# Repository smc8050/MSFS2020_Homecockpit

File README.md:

# MSFS2020 Homecockpit
The aim of this project was to build a home cockpit working together with Microsoft Flight Simulator 2020.
A "How to use it" will be published in future...

The PCB files are best viewed on [cadlab.io](https://cadlab.io/project/23795/main/files/PCB)

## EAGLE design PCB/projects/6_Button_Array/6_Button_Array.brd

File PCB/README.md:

# PCB directory
This directory contains all the PCB files, needed for the Cockpit panel. An overview will be uploaded in future...

For better visualization of the PCB's view this project on [CADLAB.io](https://cadlab.io/project/23795/main/files/PCB/projects). 

## Remarks
The zip files in the individual project folders are used to manufacture the pcb's and contain the gerber files. These will not be updated frequently, so you better build your own gerber files for production.

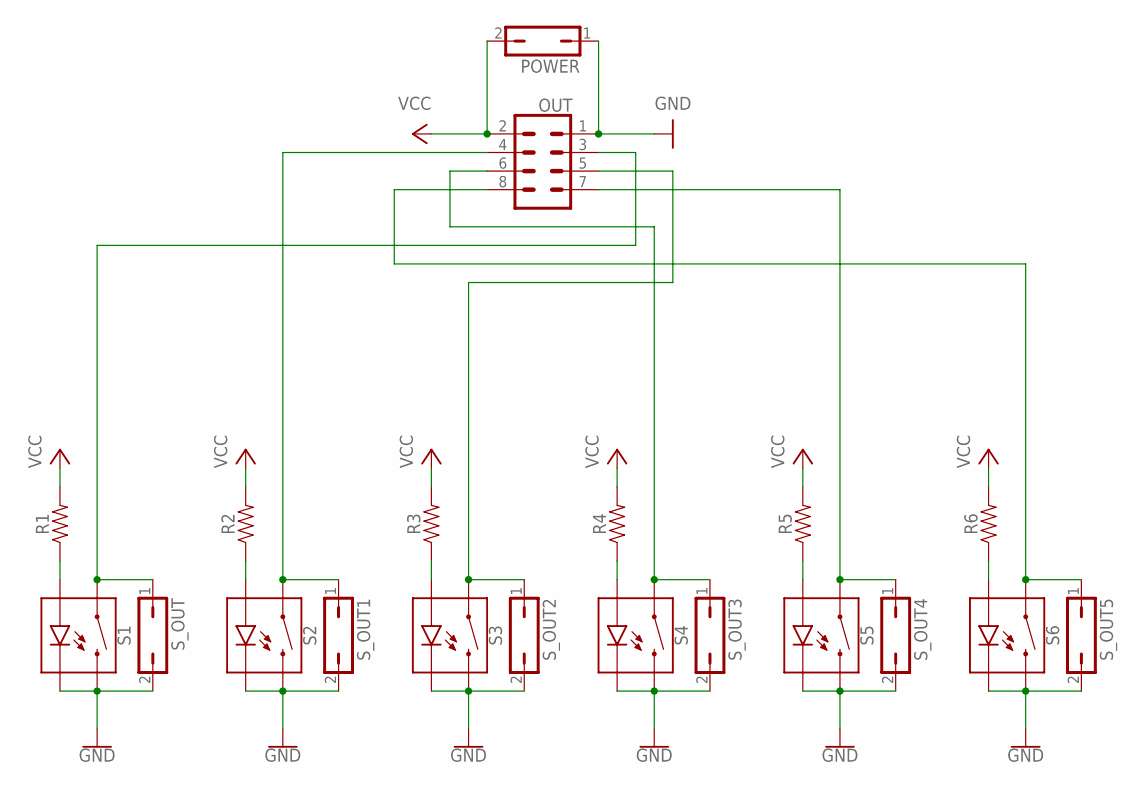
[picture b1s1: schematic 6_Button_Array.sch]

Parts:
OUT: CONN_04X2; 2X4
POWER: JP1Q; JP1
R1, R2, R3, R4, R5, R6: 1206
S1, S2, S3, S4, S5, S6: MOMENTARY-SWITCH-SPST-LED-PTH-12MM; TACTILE_SWITCH_LED_PTH_12MM
S_OUT, S_OUT1, S_OUT2, S_OUT3, S_OUT4, S_OUT5: JP1Q; JP1

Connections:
GND: OUT.1, POWER.1, S1.2, S1.C, S2.2, S2.C, S3.2, S3.C, S4.2, S4.C, S5.2, S5.C, S6.2, S6.C, S_OUT.2, S_OUT1.2, S_OUT2.2, S_OUT3.2, S_OUT4.2, S_OUT5.2
unnamed: R1.1, S1.A
unnamed: R2.1, S2.A
unnamed: R3.1, S3.A
unnamed: OUT.5, S3.4 (1), S_OUT2.1
unnamed: R4.1, S4.A
unnamed: OUT.6, S4.4 (1), S_OUT3.1
unnamed: R5.1, S5.A
unnamed: OUT.7, S5.4 (1), S_OUT4.1
unnamed: R6.1, S6.A
unnamed: OUT.3, S1.4 (1), S_OUT.1
unnamed: OUT.8, S6.4 (1), S_OUT5.1
unnamed: OUT.4, S2.4 (1), S_OUT1.1
VCC: OUT.2, POWER.2, R1.2, R2.2, R3.2, R4.2, R5.2, R6.2

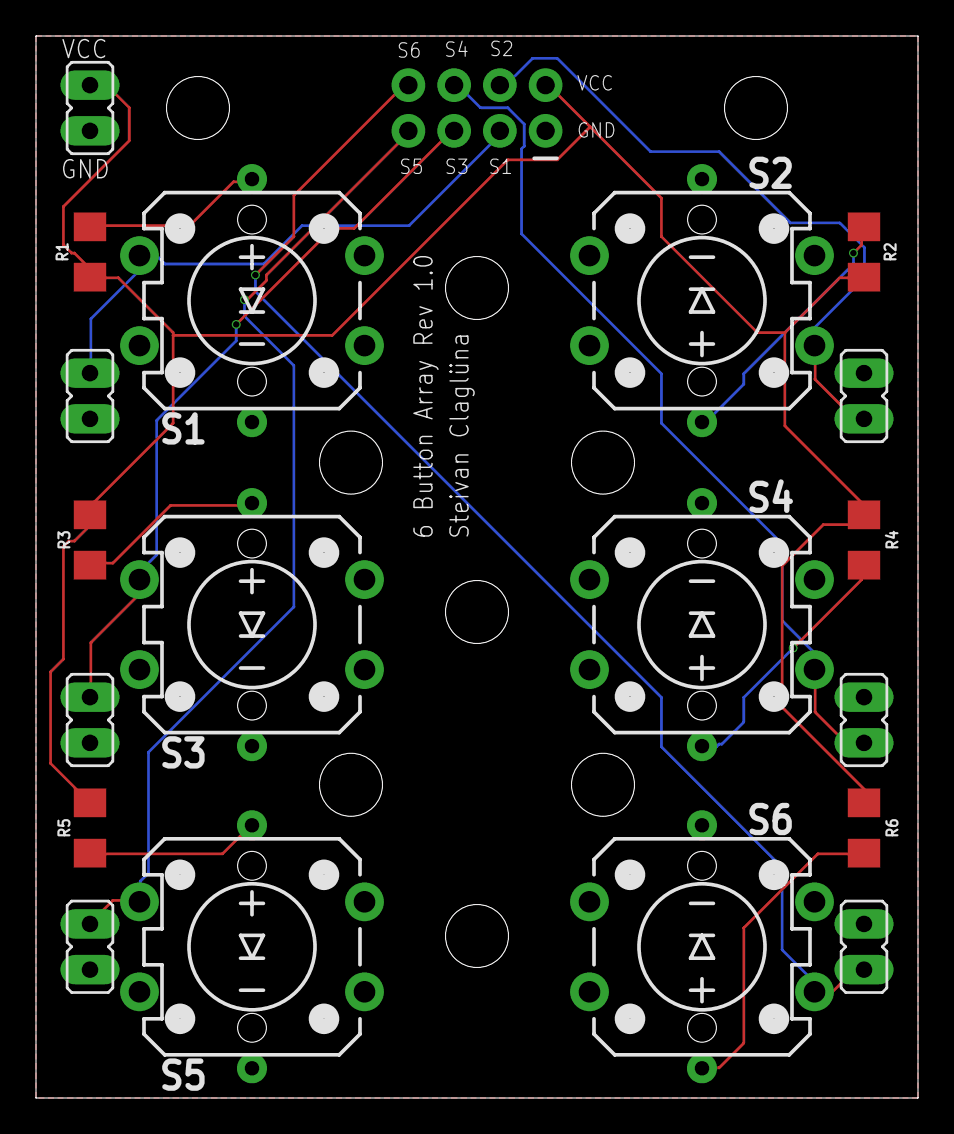
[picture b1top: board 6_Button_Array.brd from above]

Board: 2 copper layers, 49.0 x 59.0 mm, 20 parts (1 on the bottom side), 14 nets.

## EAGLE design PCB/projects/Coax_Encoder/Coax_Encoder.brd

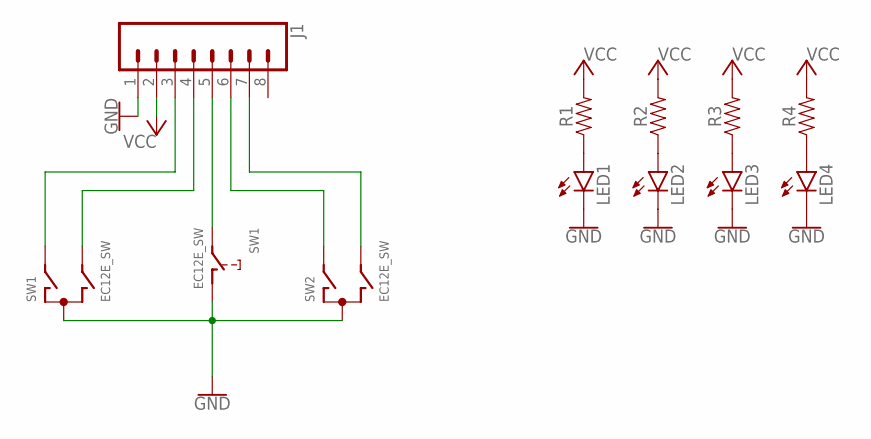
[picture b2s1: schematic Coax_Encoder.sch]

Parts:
J1: CONN_08"; 1X08
LED1, LED2, LED3, LED4: LED3MM
R1, R2, R3, R4: 1206
SW1, SW2: EC12E_SW; ALPS_EC12E_SW

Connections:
GND: J1.1, LED1.K (C), LED2.K (C), LED3.K (C), LED4.K (C), SW1.C, SW1.D (1), SW2.C
unnamed: J1.3, SW1.A
unnamed: J1.4, SW1.B
unnamed: J1.5, SW1.E (2)
unnamed: J1.6, SW2.A
unnamed: J1.7, SW2.B
unnamed: LED1.A, R1.1
unnamed: LED2.A, R2.1
unnamed: LED3.A, R3.1
unnamed: LED4.A, R4.1
VCC: J1.2, R1.2, R2.2, R3.2, R4.2

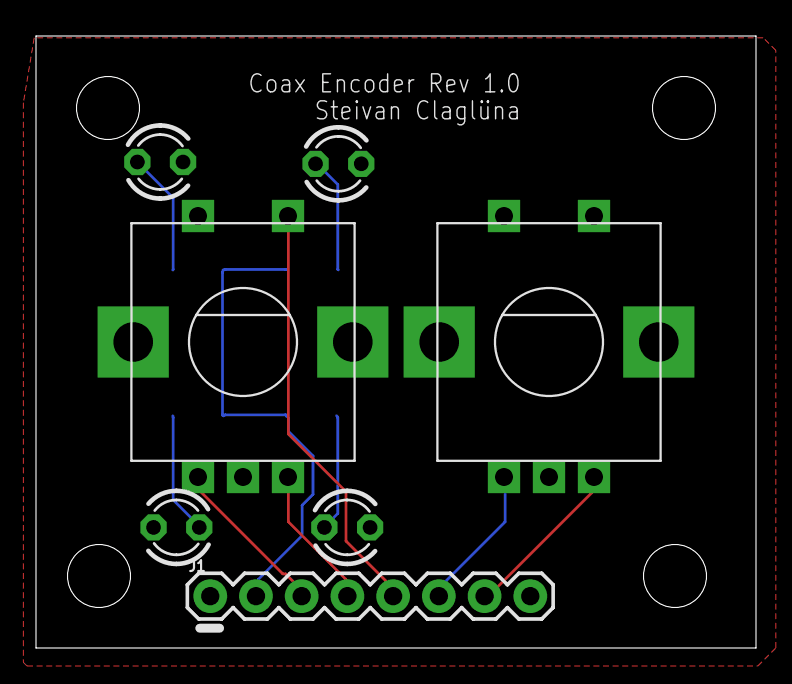
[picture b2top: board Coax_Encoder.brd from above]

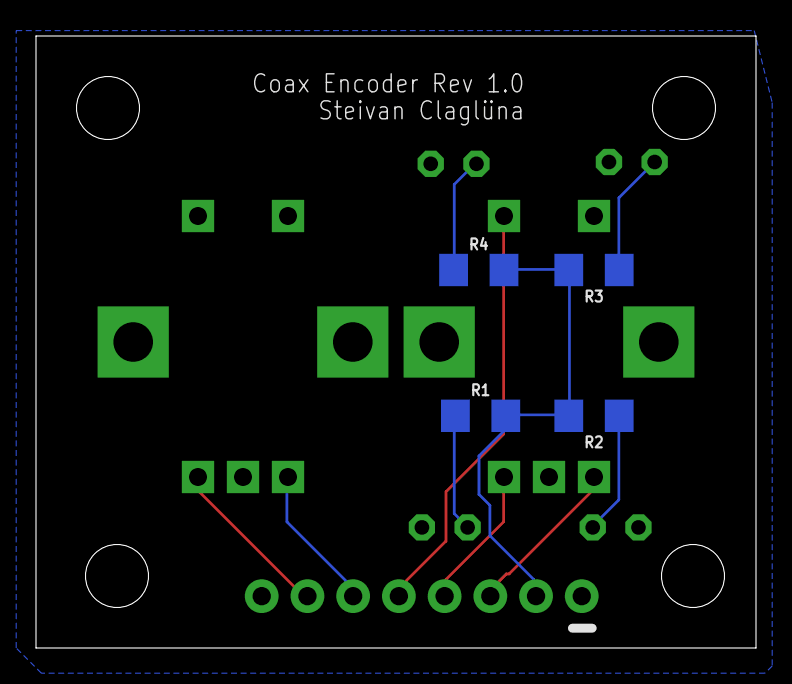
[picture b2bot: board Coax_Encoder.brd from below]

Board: 2 copper layers, 40.0 x 34.0 mm, 11 parts (4 on the bottom side), 11 nets.

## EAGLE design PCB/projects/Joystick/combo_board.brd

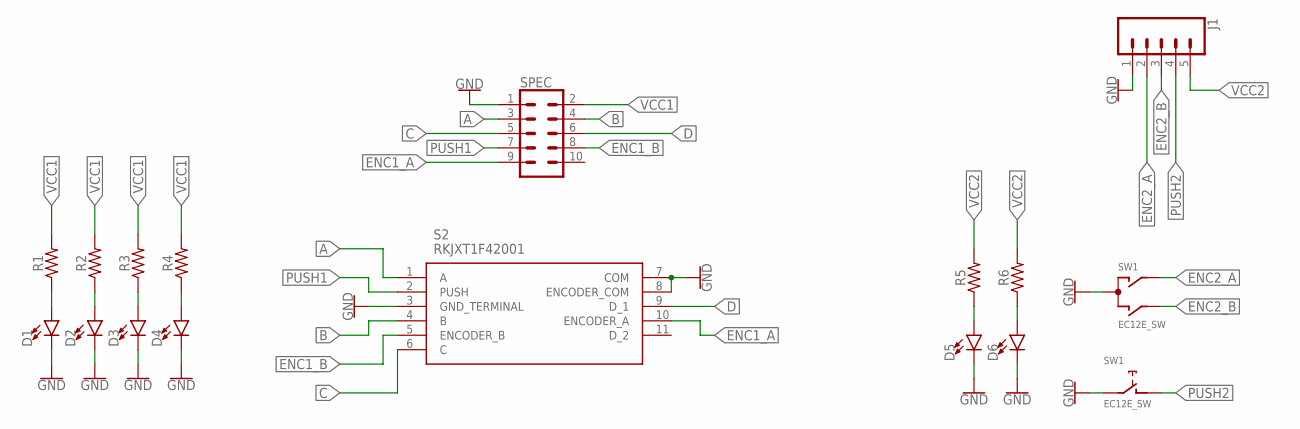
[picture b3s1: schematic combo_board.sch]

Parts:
D1, D2, D3, D4, D5, D6: LED-3MM-NO_SILK; LED_3MM-NS
J1: CONN_05; 1X05
R1, R2, R3, R4, R5, R6: 1206
S2: RKJXT1F42001
SPEC: CONN_05X2PTH; 2X5
SW1: EC12E_SW; ALPS_EC12E_SW

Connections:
A: S2.1 (A), SPEC.3
B: S2.4 (B), SPEC.4
C: S2.6 (C), SPEC.5
D: S2.9 (D_1), SPEC.6
ENC1_A: S2.10 (ENCODER_A), SPEC.9
ENC1_B: S2.5 (ENCODER_B), SPEC.8
ENC2_A: J1.2, SW1.A
ENC2_B: J1.3, SW1.B
GND: D1.K (C), D2.K (C), D3.K (C), D4.K (C), D5.K (C), D6.K (C), J1.1, S2.3 (GND_TERMINAL), S2.7 (COM), S2.8 (ENCODER_COM), SPEC.1, SW1.C, SW1.E (2)
unnamed: D1.A, R1.1
unnamed: D2.A, R2.1
unnamed: D3.A, R3.1
unnamed: D4.A, R4.1
unnamed: D5.A, R5.1
unnamed: D6.A, R6.1
PUSH1: S2.2 (PUSH), SPEC.7
PUSH2: J1.4, SW1.D (1)
VCC1: R1.2, R2.2, R3.2, R4.2, SPEC.2
VCC2: J1.5, R5.2, R6.2

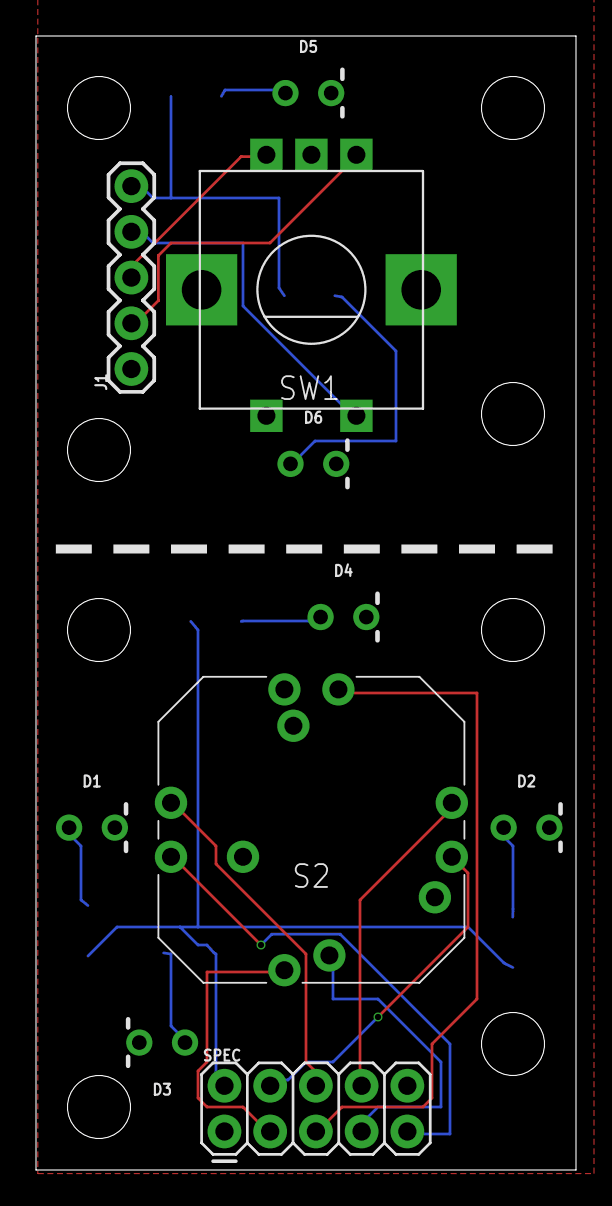
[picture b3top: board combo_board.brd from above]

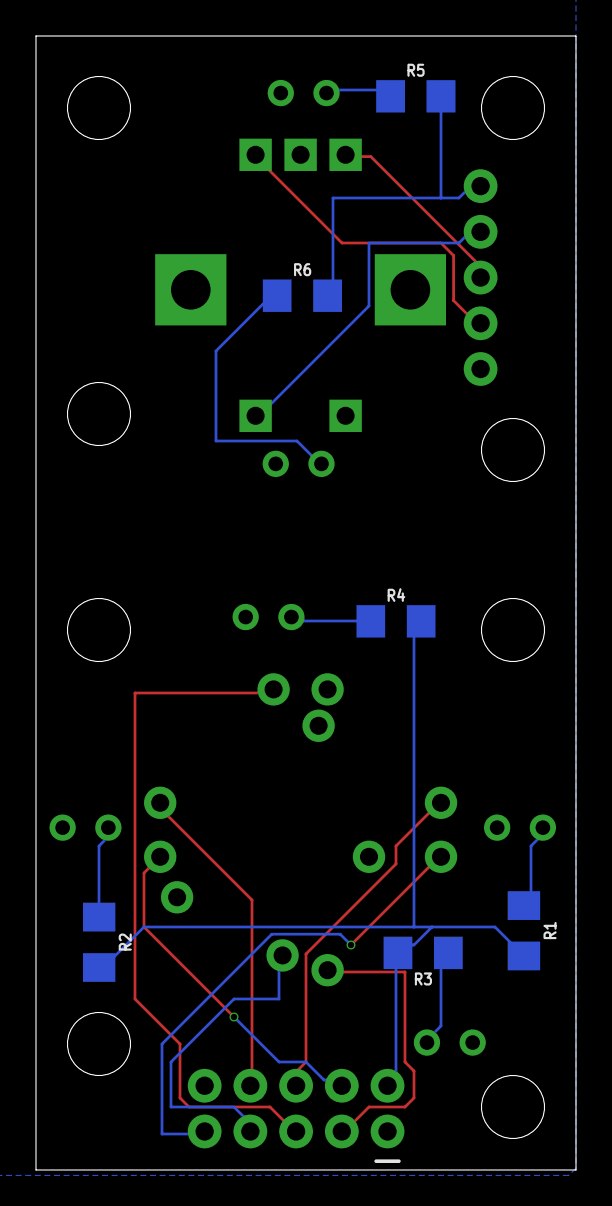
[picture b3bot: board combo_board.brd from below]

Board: 2 copper layers, 30.0 x 63.0 mm, 16 parts (6 on the bottom side), 19 nets.

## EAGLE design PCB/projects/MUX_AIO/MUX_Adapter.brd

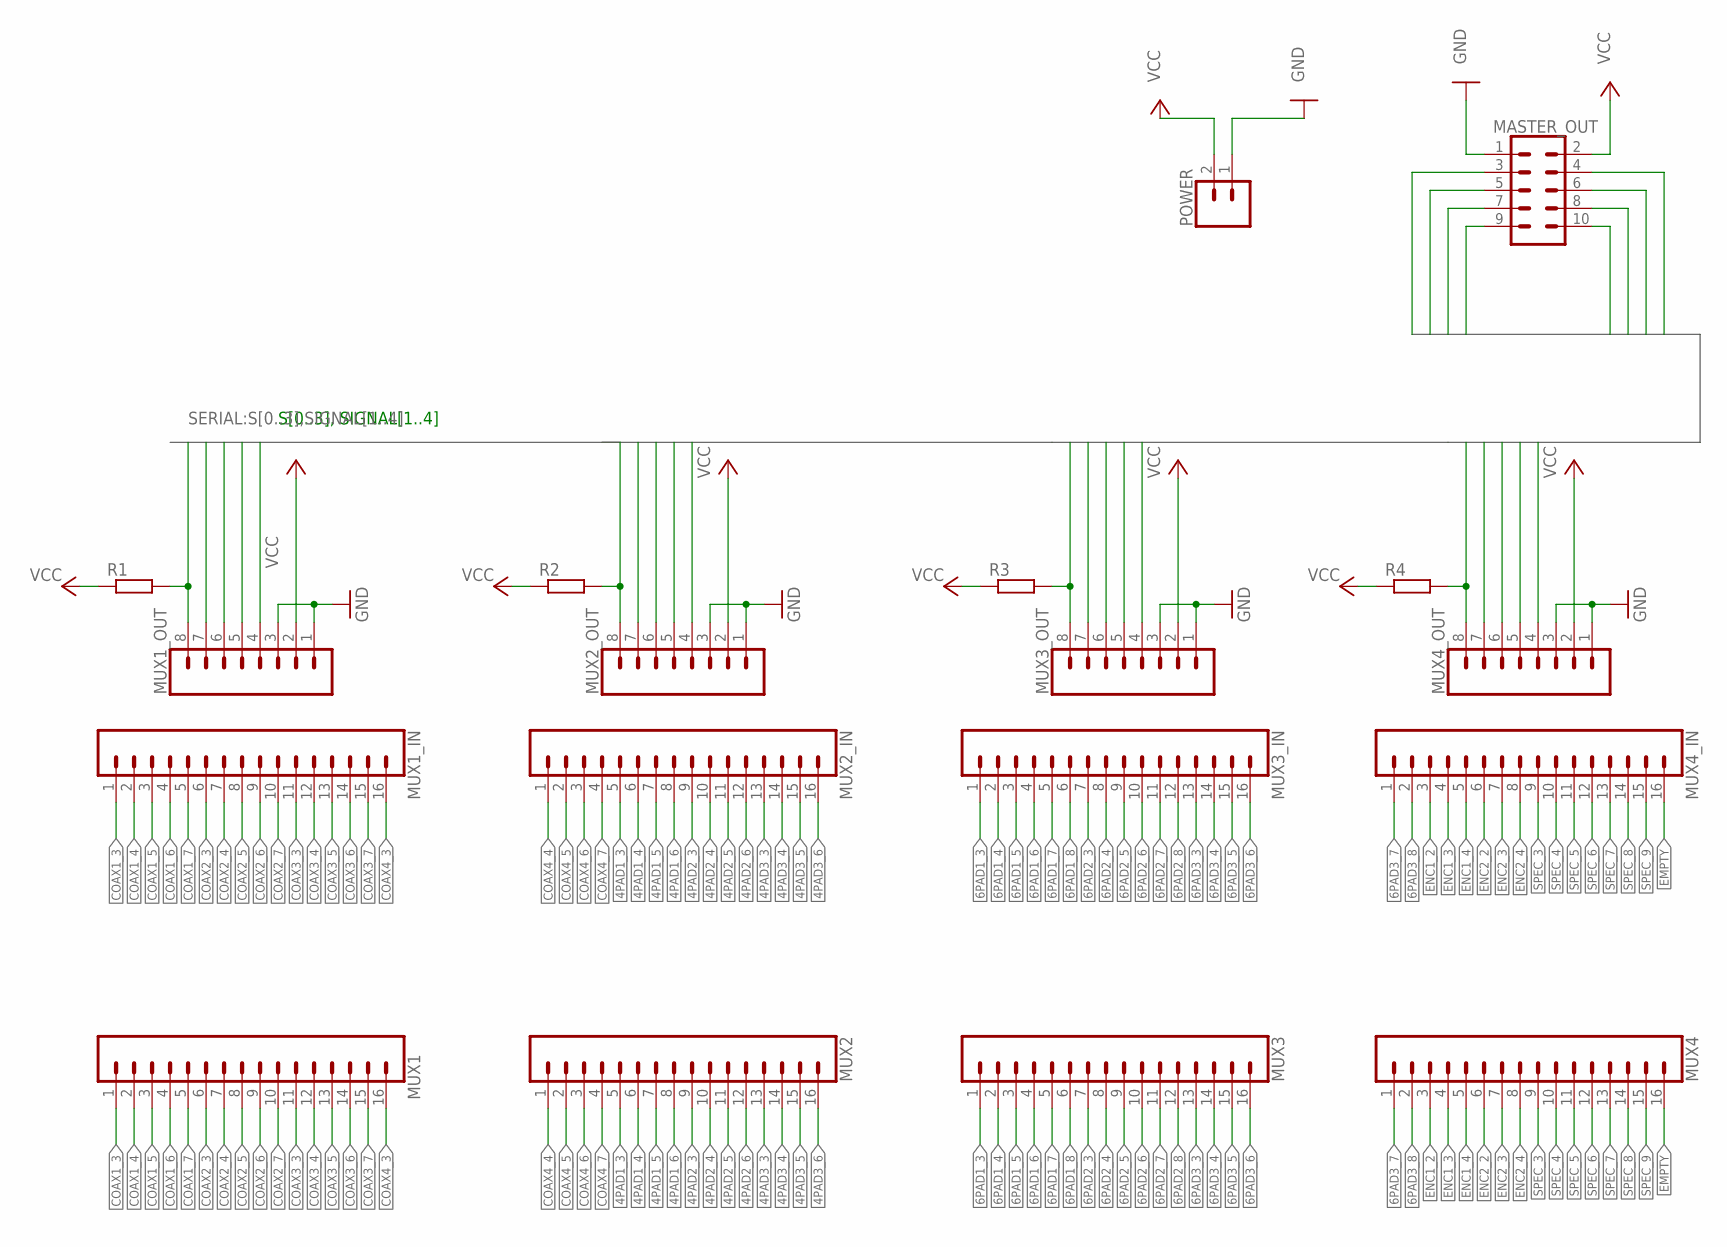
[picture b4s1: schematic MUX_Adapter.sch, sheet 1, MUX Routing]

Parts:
MASTER_OUT: CONN_05X2SHD-NS; 2X5-SHROUDED-NS
MUX1, MUX1_IN, MUX2, MUX2_IN, MUX3, MUX3_IN, MUX4, MUX4_IN: CONN_16; 1X16
MUX1_OUT, MUX2_OUT, MUX3_OUT, MUX4_OUT: CONN_08"; 1X08
POWER: CONN_02; 1X02
R1, R2, R3, R4: R-EU_0207/10; 0207/10

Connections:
4PAD1_3: MUX2.5, MUX2_IN.5; also elsewhere on the board
4PAD1_4: MUX2.6, MUX2_IN.6; also elsewhere on the board
4PAD1_5: MUX2.7, MUX2_IN.7; also elsewhere on the board
4PAD1_6: MUX2.8, MUX2_IN.8; also elsewhere on the board
4PAD2_3: MUX2.9, MUX2_IN.9; also elsewhere on the board
4PAD2_4: MUX2.10, MUX2_IN.10; also elsewhere on the board
4PAD2_5: MUX2.11, MUX2_IN.11; also elsewhere on the board
4PAD2_6: MUX2.12, MUX2_IN.12; also elsewhere on the board
4PAD3_3: MUX2.13, MUX2_IN.13; also elsewhere on the board
4PAD3_4: MUX2.14, MUX2_IN.14; also elsewhere on the board
4PAD3_5: MUX2.15, MUX2_IN.15; also elsewhere on the board
4PAD3_6: MUX2.16, MUX2_IN.16; also elsewhere on the board
6PAD1_3: MUX3.1, MUX3_IN.1; also elsewhere on the board
6PAD1_4: MUX3.2, MUX3_IN.2; also elsewhere on the board
6PAD1_5: MUX3.3, MUX3_IN.3; also elsewhere on the board
6PAD1_6: MUX3.4, MUX3_IN.4; also elsewhere on the board
6PAD1_7: MUX3.5, MUX3_IN.5; also elsewhere on the board
6PAD1_8: MUX3.6, MUX3_IN.6; also elsewhere on the board
6PAD2_3: MUX3.7, MUX3_IN.7; also elsewhere on the board
6PAD2_4: MUX3.8, MUX3_IN.8; also elsewhere on the board
6PAD2_5: MUX3.9, MUX3_IN.9; also elsewhere on the board
6PAD2_6: MUX3.10, MUX3_IN.10; also elsewhere on the board
6PAD2_7: MUX3.11, MUX3_IN.11; also elsewhere on the board
6PAD2_8: MUX3.12, MUX3_IN.12; also elsewhere on the board
6PAD3_3: MUX3.13, MUX3_IN.13; also elsewhere on the board
6PAD3_4: MUX3.14, MUX3_IN.14; also elsewhere on the board
6PAD3_5: MUX3.15, MUX3_IN.15; also elsewhere on the board
6PAD3_6: MUX3.16, MUX3_IN.16; also elsewhere on the board
6PAD3_7: MUX4.1, MUX4_IN.1; also elsewhere on the board
6PAD3_8: MUX4.2, MUX4_IN.2; also elsewhere on the board
COAX1_3: MUX1.1, MUX1_IN.1; also elsewhere on the board
COAX1_4: MUX1.2, MUX1_IN.2; also elsewhere on the board
COAX1_5: MUX1.3, MUX1_IN.3; also elsewhere on the board
COAX1_6: MUX1.4, MUX1_IN.4; also elsewhere on the board
COAX1_7: MUX1.5, MUX1_IN.5; also elsewhere on the board
COAX2_3: MUX1.6, MUX1_IN.6; also elsewhere on the board
COAX2_4: MUX1.7, MUX1_IN.7; also elsewhere on the board
COAX2_5: MUX1.8, MUX1_IN.8; also elsewhere on the board
COAX2_6: MUX1.9, MUX1_IN.9; also elsewhere on the board
COAX2_7: MUX1.10, MUX1_IN.10; also elsewhere on the board
COAX3_3: MUX1.11, MUX1_IN.11; also elsewhere on the board
COAX3_4: MUX1.12, MUX1_IN.12; also elsewhere on the board
COAX3_5: MUX1.13, MUX1_IN.13; also elsewhere on the board
COAX3_6: MUX1.14, MUX1_IN.14; also elsewhere on the board
COAX3_7: MUX1.15, MUX1_IN.15; also elsewhere on the board
COAX4_3: MUX1.16, MUX1_IN.16; also elsewhere on the board
COAX4_4: MUX2.1, MUX2_IN.1; also elsewhere on the board
COAX4_5: MUX2.2, MUX2_IN.2; also elsewhere on the board
COAX4_6: MUX2.3, MUX2_IN.3; also elsewhere on the board
COAX4_7: MUX2.4, MUX2_IN.4; also elsewhere on the board
EMPTY: MUX4.16, MUX4_IN.16
ENC1_2: MUX4.3, MUX4_IN.3; also elsewhere on the board
ENC1_3: MUX4.4, MUX4_IN.4; also elsewhere on the board
ENC1_4: MUX4.5, MUX4_IN.5; also elsewhere on the board
ENC2_2: MUX4.6, MUX4_IN.6; also elsewhere on the board
ENC2_3: MUX4.7, MUX4_IN.7; also elsewhere on the board
ENC2_4: MUX4.8, MUX4_IN.8; also elsewhere on the board
GND: MASTER_OUT.1, MUX1_OUT.1, MUX1_OUT.3, MUX2_OUT.1, MUX2_OUT.3, MUX3_OUT.1, MUX3_OUT.3, MUX4_OUT.1, MUX4_OUT.3, POWER.1; also elsewhere on the board
S0: MASTER_OUT.3, MUX1_OUT.4, MUX2_OUT.4, MUX3_OUT.4, MUX4_OUT.4
S1: MASTER_OUT.4, MUX1_OUT.5, MUX2_OUT.5, MUX3_OUT.5, MUX4_OUT.5
S2: MASTER_OUT.5, MUX1_OUT.6, MUX2_OUT.6, MUX3_OUT.6, MUX4_OUT.6
S3: MASTER_OUT.6, MUX1_OUT.7, MUX2_OUT.7, MUX3_OUT.7, MUX4_OUT.7
SIGNAL1: MASTER_OUT.7, MUX4_OUT.8, R4.2
SIGNAL2: MASTER_OUT.8, MUX3_OUT.8, R3.2
SIGNAL3: MASTER_OUT.9, MUX2_OUT.8, R2.2
SIGNAL4: MASTER_OUT.10, MUX1_OUT.8, R1.2
SPEC_3: MUX4.9, MUX4_IN.9; also elsewhere on the board
SPEC_4: MUX4.10, MUX4_IN.10; also elsewhere on the board
SPEC_5: MUX4.11, MUX4_IN.11; also elsewhere on the board
SPEC_6: MUX4.12, MUX4_IN.12; also elsewhere on the board
SPEC_7: MUX4.13, MUX4_IN.13; also elsewhere on the board
SPEC_8: MUX4.14, MUX4_IN.14; also elsewhere on the board
SPEC_9: MUX4.15, MUX4_IN.15; also elsewhere on the board
VCC: MASTER_OUT.2, MUX1_OUT.2, MUX2_OUT.2, MUX3_OUT.2, MUX4_OUT.2, POWER.2, R1.1, R2.1, R3.1, R4.1; also elsewhere on the board

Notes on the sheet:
S[0..3], SIGNAL[1..4]

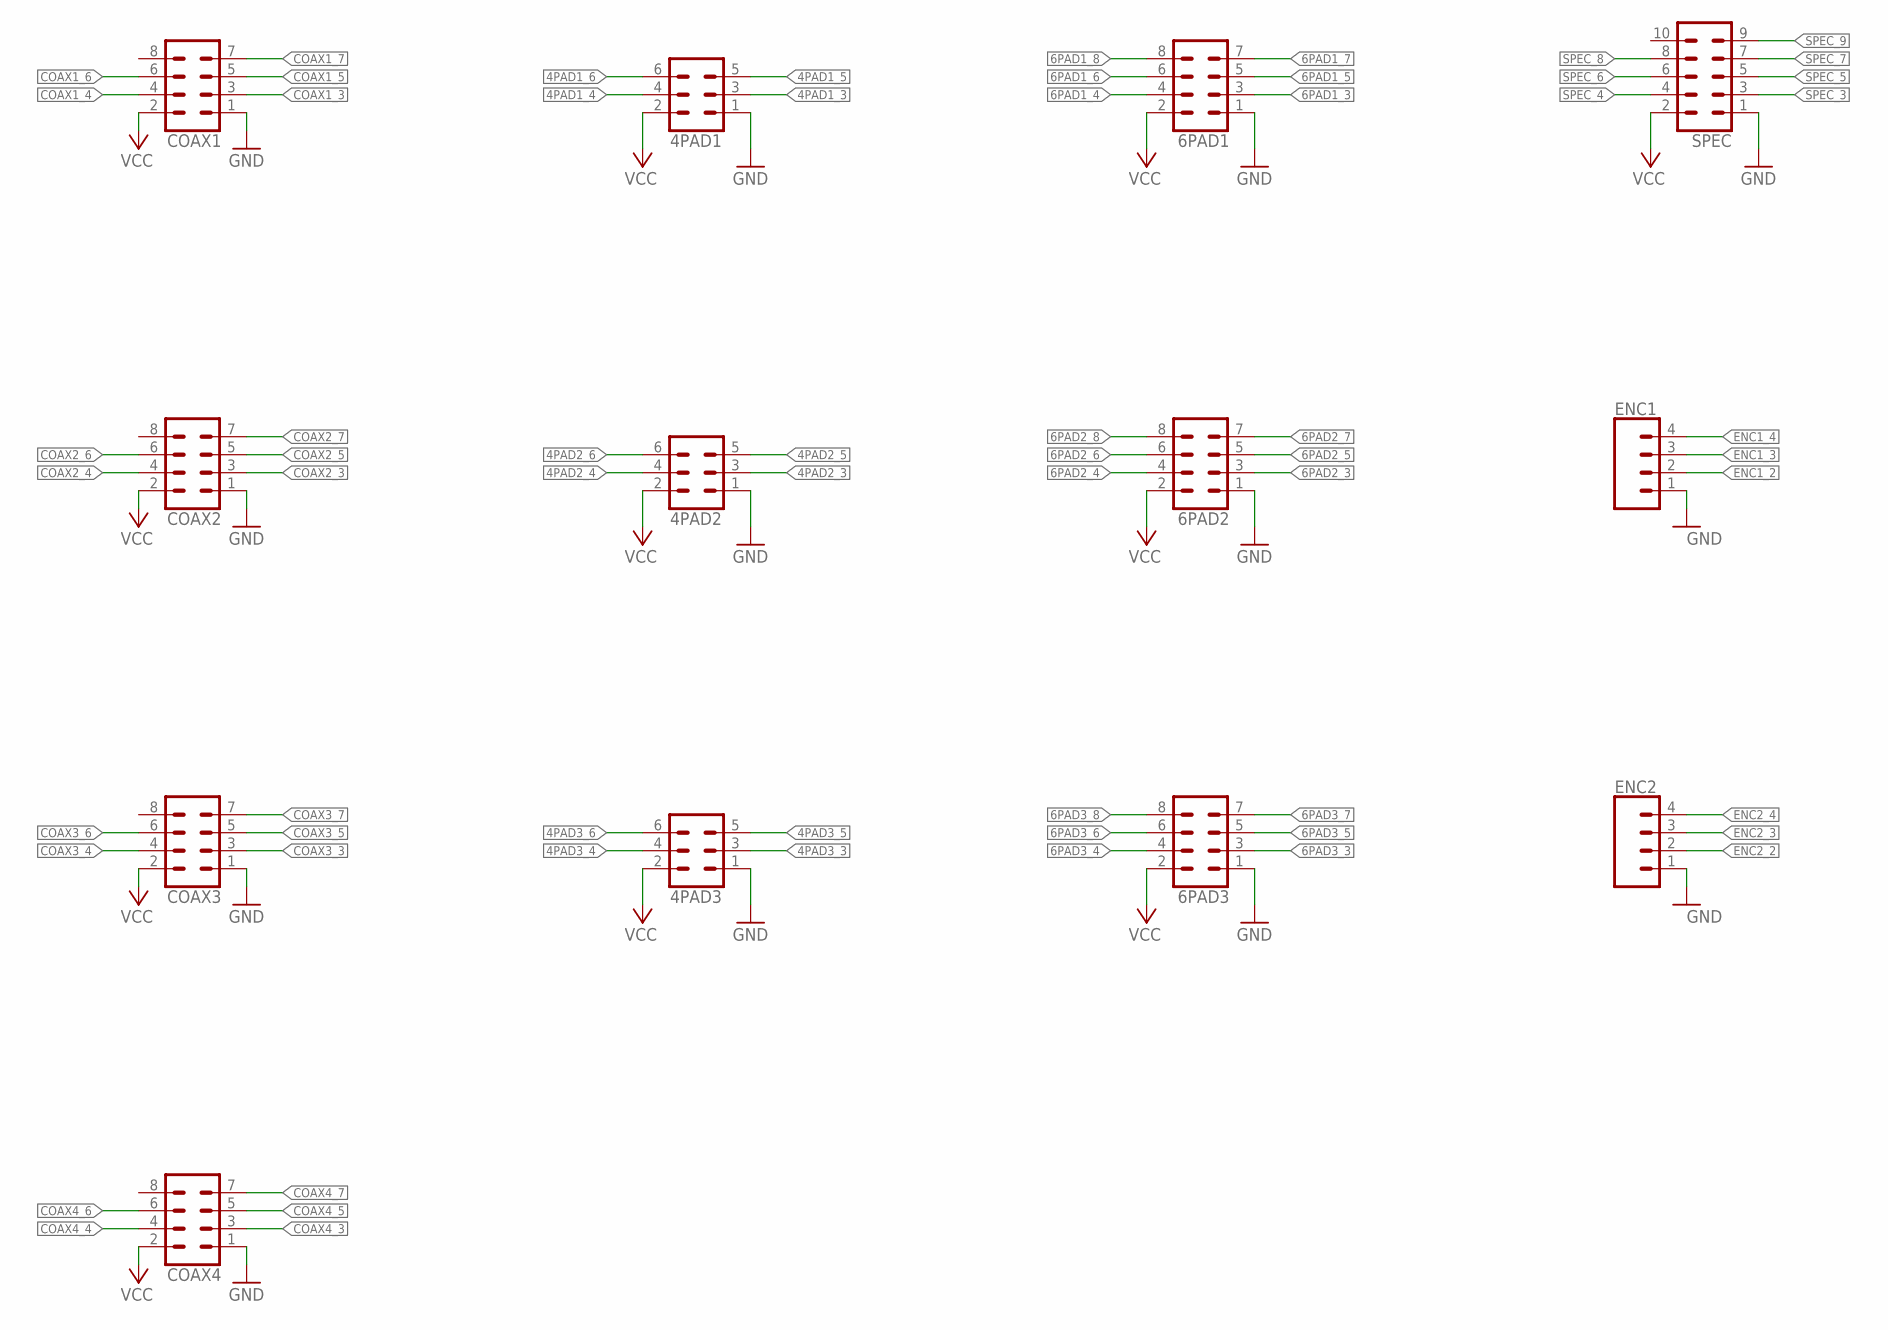
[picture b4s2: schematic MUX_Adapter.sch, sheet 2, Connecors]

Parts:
4PAD1, 4PAD2, 4PAD3: CONN_03X2NO_SILK; 2X3-NS
6PAD1, 6PAD2, 6PAD3: CONN_04X2; 2X4
COAX1, COAX2, COAX3, COAX4: CONN_04X2; 2X4
ENC1, ENC2: CONN_04PTH; 1X04
SPEC: CONN_05X2PTH; 2X5

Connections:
4PAD1_3: 4PAD1.3; also elsewhere on the board
4PAD1_4: 4PAD1.4; also elsewhere on the board
4PAD1_5: 4PAD1.5; also elsewhere on the board
4PAD1_6: 4PAD1.6; also elsewhere on the board
4PAD2_3: 4PAD2.3; also elsewhere on the board
4PAD2_4: 4PAD2.4; also elsewhere on the board
4PAD2_5: 4PAD2.5; also elsewhere on the board
4PAD2_6: 4PAD2.6; also elsewhere on the board
4PAD3_3: 4PAD3.3; also elsewhere on the board
4PAD3_4: 4PAD3.4; also elsewhere on the board
4PAD3_5: 4PAD3.5; also elsewhere on the board
4PAD3_6: 4PAD3.6; also elsewhere on the board
6PAD1_3: 6PAD1.3; also elsewhere on the board
6PAD1_4: 6PAD1.4; also elsewhere on the board
6PAD1_5: 6PAD1.5; also elsewhere on the board
6PAD1_6: 6PAD1.6; also elsewhere on the board
6PAD1_7: 6PAD1.7; also elsewhere on the board
6PAD1_8: 6PAD1.8; also elsewhere on the board
6PAD2_3: 6PAD2.3; also elsewhere on the board
6PAD2_4: 6PAD2.4; also elsewhere on the board
6PAD2_5: 6PAD2.5; also elsewhere on the board
6PAD2_6: 6PAD2.6; also elsewhere on the board
6PAD2_7: 6PAD2.7; also elsewhere on the board
6PAD2_8: 6PAD2.8; also elsewhere on the board
6PAD3_3: 6PAD3.3; also elsewhere on the board
6PAD3_4: 6PAD3.4; also elsewhere on the board
6PAD3_5: 6PAD3.5; also elsewhere on the board
6PAD3_6: 6PAD3.6; also elsewhere on the board
6PAD3_7: 6PAD3.7; also elsewhere on the board
6PAD3_8: 6PAD3.8; also elsewhere on the board
COAX1_3: COAX1.3; also elsewhere on the board
COAX1_4: COAX1.4; also elsewhere on the board
COAX1_5: COAX1.5; also elsewhere on the board
COAX1_6: COAX1.6; also elsewhere on the board
COAX1_7: COAX1.7; also elsewhere on the board
COAX2_3: COAX2.3; also elsewhere on the board
COAX2_4: COAX2.4; also elsewhere on the board
COAX2_5: COAX2.5; also elsewhere on the board
COAX2_6: COAX2.6; also elsewhere on the board
COAX2_7: COAX2.7; also elsewhere on the board
COAX3_3: COAX3.3; also elsewhere on the board
COAX3_4: COAX3.4; also elsewhere on the board
COAX3_5: COAX3.5; also elsewhere on the board
COAX3_6: COAX3.6; also elsewhere on the board
COAX3_7: COAX3.7; also elsewhere on the board
COAX4_3: COAX4.3; also elsewhere on the board
COAX4_4: COAX4.4; also elsewhere on the board
COAX4_5: COAX4.5; also elsewhere on the board
COAX4_6: COAX4.6; also elsewhere on the board
COAX4_7: COAX4.7; also elsewhere on the board
ENC1_2: ENC1.2; also elsewhere on the board
ENC1_3: ENC1.3; also elsewhere on the board
ENC1_4: ENC1.4; also elsewhere on the board
ENC2_2: ENC2.2; also elsewhere on the board
ENC2_3: ENC2.3; also elsewhere on the board
ENC2_4: ENC2.4; also elsewhere on the board
GND: 4PAD1.1, 4PAD2.1, 4PAD3.1, 6PAD1.1, 6PAD2.1, 6PAD3.1, COAX1.1, COAX2.1, COAX3.1, COAX4.1, ENC1.1, ENC2.1, SPEC.1; also elsewhere on the board
SPEC_3: SPEC.3; also elsewhere on the board
SPEC_4: SPEC.4; also elsewhere on the board
SPEC_5: SPEC.5; also elsewhere on the board
SPEC_6: SPEC.6; also elsewhere on the board
SPEC_7: SPEC.7; also elsewhere on the board
SPEC_8: SPEC.8; also elsewhere on the board
SPEC_9: SPEC.9; also elsewhere on the board
VCC: 4PAD1.2, 4PAD2.2, 4PAD3.2, 6PAD1.2, 6PAD2.2, 6PAD3.2, COAX1.2, COAX2.2, COAX3.2, COAX4.2, SPEC.2; also elsewhere on the board

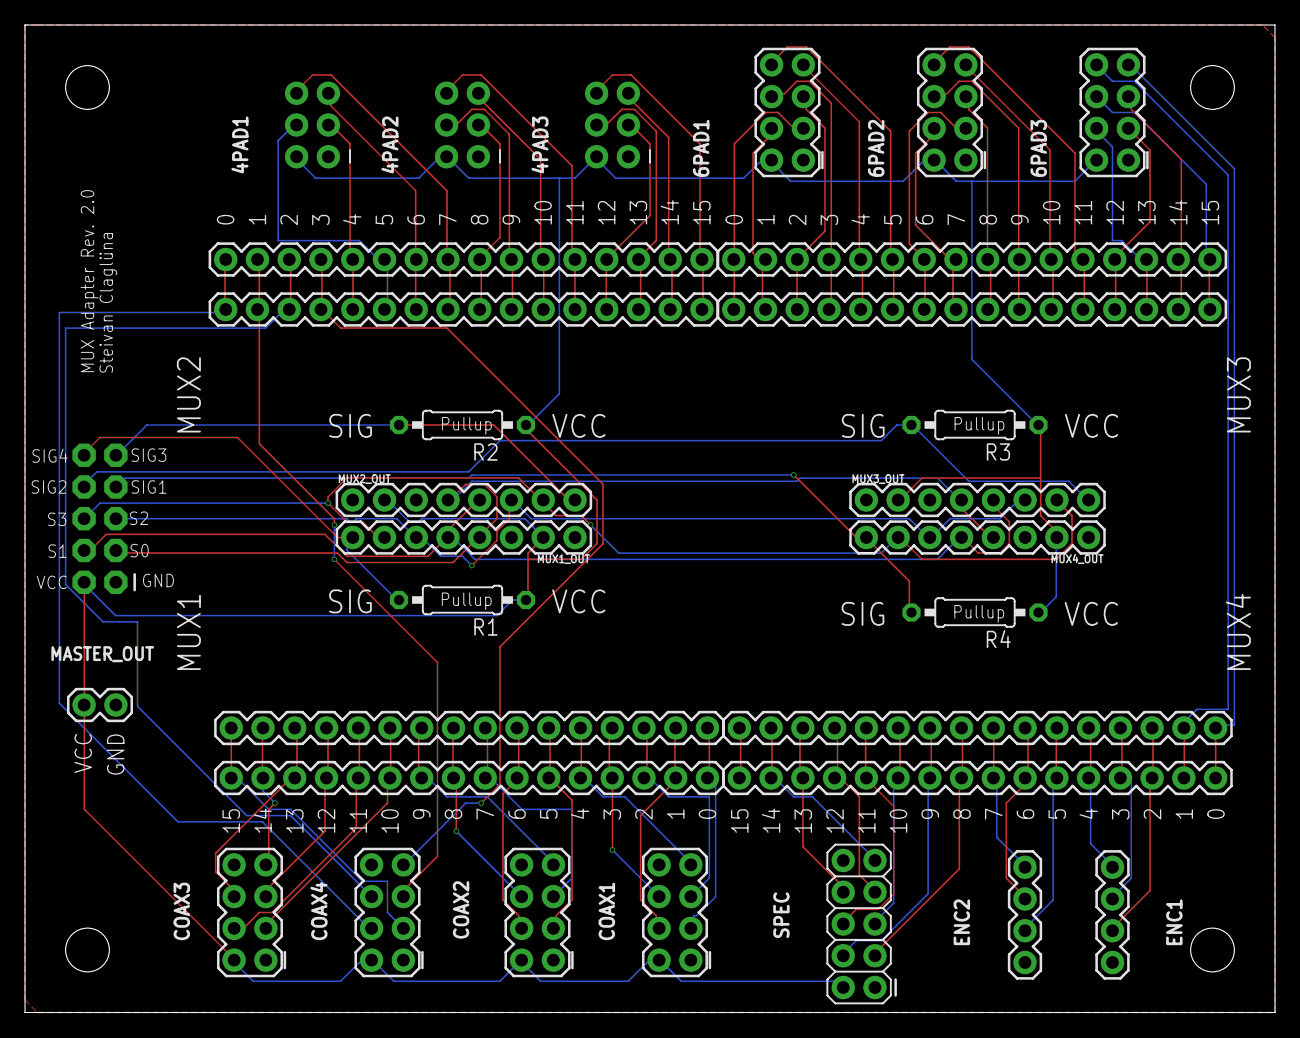
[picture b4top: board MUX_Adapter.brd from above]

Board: 2 copper layers, 100.0 x 79.0 mm, 31 parts (0 on the bottom side), 74 nets.

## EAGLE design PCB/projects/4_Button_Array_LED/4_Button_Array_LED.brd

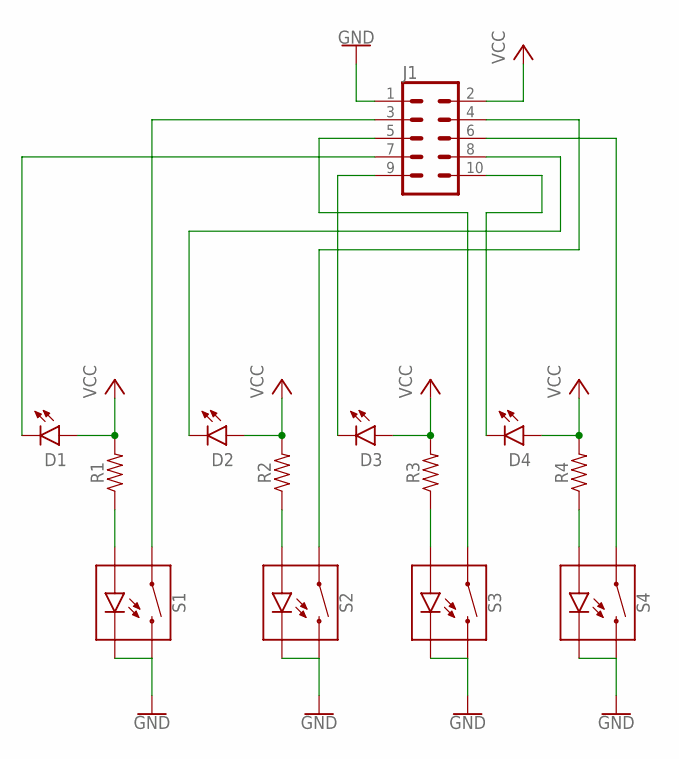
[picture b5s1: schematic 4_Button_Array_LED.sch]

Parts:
D1, D2, D3, D4: LED3MM; LED_3MM
J1: CONN_05X2SHD-NS; 2X5-SHROUDED-NS
R1, R2, R3, R4: 1206
S1, S2, S3, S4: MOMENTARY-SWITCH-SPST-LED-PTH-12MM; TACTILE_SWITCH_LED_PTH_12MM

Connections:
GND: J1.1, S1.2, S1.C, S2.2, S2.C, S3.2, S3.C, S4.2, S4.C
unnamed: R2.1, S2.A
unnamed: R1.1, S1.A
unnamed: R3.1, S3.A
unnamed: R4.1, S4.A
unnamed: J1.3, S1.4 (1)
unnamed: J1.4, S2.4 (1)
unnamed: J1.5, S3.4 (1)
unnamed: J1.6, S4.4 (1)
unnamed: D1.K (C), J1.7
unnamed: D2.K (C), J1.8
unnamed: D3.K (C), J1.9
unnamed: D4.K (C), J1.10
VCC: D1.A, D2.A, D3.A, D4.A, J1.2, R1.2, R2.2, R3.2, R4.2

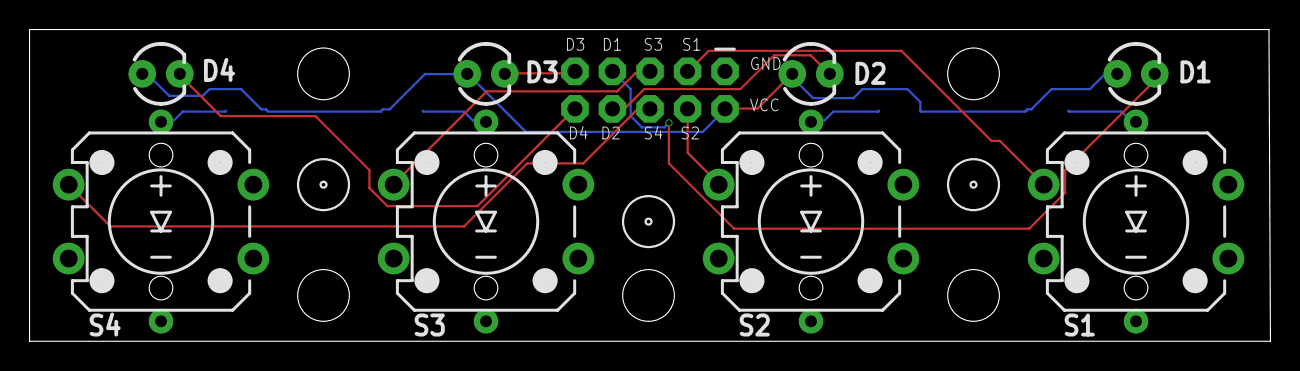
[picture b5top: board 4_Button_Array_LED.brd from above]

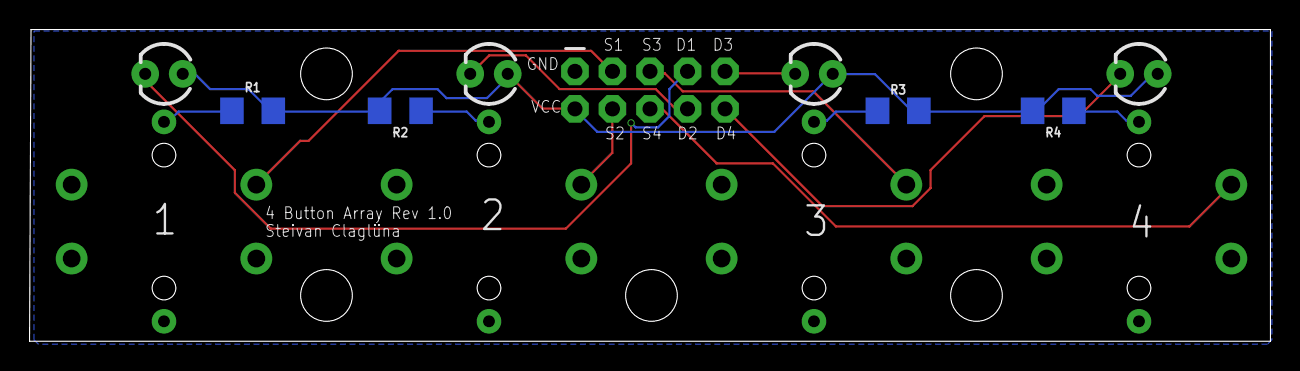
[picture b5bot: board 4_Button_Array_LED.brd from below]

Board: 2 copper layers, 84.0 x 21.1 mm, 13 parts (4 on the bottom side), 14 nets.

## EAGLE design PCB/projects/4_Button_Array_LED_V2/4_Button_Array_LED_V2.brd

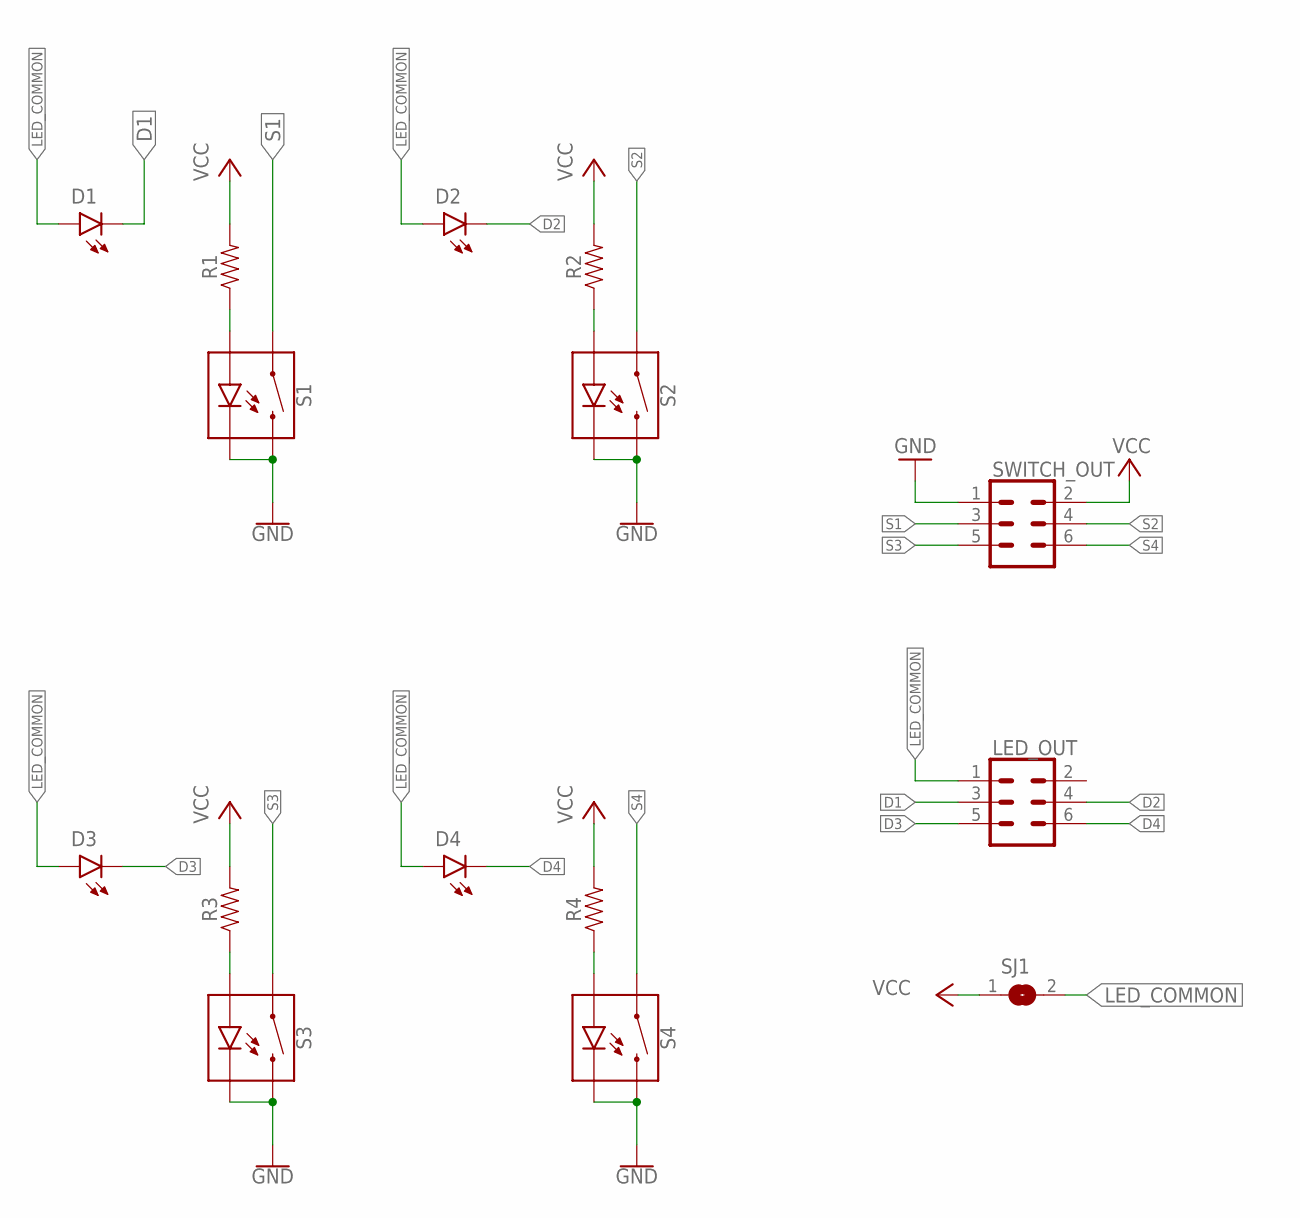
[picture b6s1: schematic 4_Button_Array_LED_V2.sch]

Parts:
D1, D2, D3, D4: LED3MM; LED_3MM
LED_OUT: CONN_03X2SHROUD; 2X3-SHROUDED
R1, R2, R3, R4: 1206
S1, S2, S3, S4: MOMENTARY-SWITCH-SPST-LED-PTH-12MM; TACTILE_SWITCH_LED_PTH_12MM
SJ1: SJ
SWITCH_OUT: CONN_03X2SHROUD; 2X3-SHROUDED

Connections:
D1: D1.K (C), LED_OUT.3
D2: D2.K (C), LED_OUT.4
D3: D3.K (C), LED_OUT.5
D4: D4.K (C), LED_OUT.6
GND: S1.2, S1.C, S2.2, S2.C, S3.2, S3.C, S4.2, S4.C, SWITCH_OUT.1
LED_COMMON: D1.A, D2.A, D3.A, D4.A, LED_OUT.1, SJ1.2
unnamed: R2.1, S2.A
unnamed: R1.1, S1.A
unnamed: R3.1, S3.A
unnamed: R4.1, S4.A
S1: S1.4 (1), SWITCH_OUT.3
S2: S2.4 (1), SWITCH_OUT.4
S3: S3.4 (1), SWITCH_OUT.5
S4: S4.4 (1), SWITCH_OUT.6
VCC: R1.2, R2.2, R3.2, R4.2, SJ1.1, SWITCH_OUT.2

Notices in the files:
parts and their libraries:
SparkFun-LED: Licensing: Creative Commons ShareAlike 4.0 International - https://creativecommons.org/licenses/by-sa/4.0
